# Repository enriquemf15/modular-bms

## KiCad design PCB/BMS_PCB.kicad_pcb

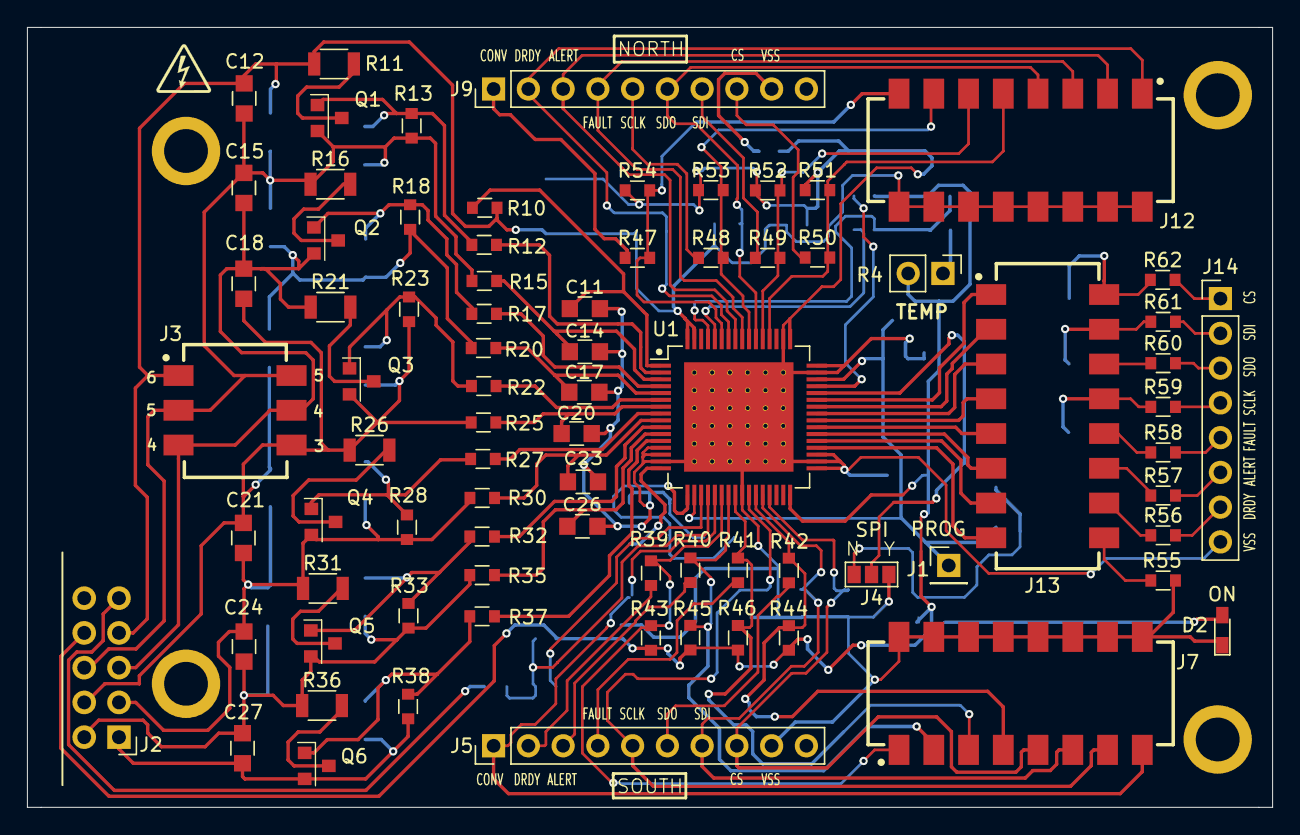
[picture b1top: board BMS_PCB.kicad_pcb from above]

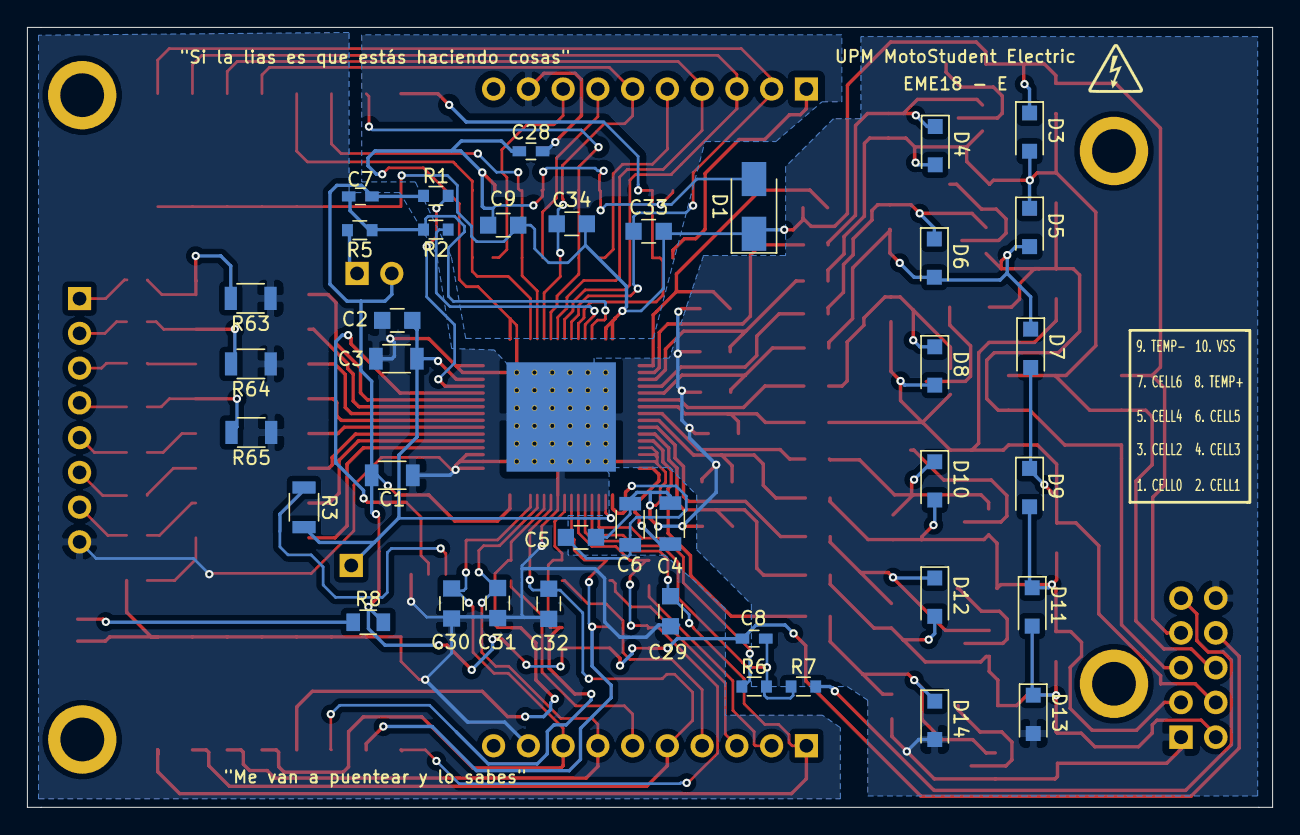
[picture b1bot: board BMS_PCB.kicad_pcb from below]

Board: 2 copper layers, 91.0 x 57.0 mm, 118 parts (39 on the bottom side), 93 nets.

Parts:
C1, C3, C6: 2,2 uF; C_1206
C2, C5, C9, C12, C15, C18, C21, C24, C27: 0,1 uF; C_0805_HandSoldering
C4: 10 uF; C_1206
C7, C8: 47 nF; C_0603_HandSoldering
C11, C14, C17, C20, C23, C26: 2.2 uF; C_0805_HandSoldering
C28: 10 nF; C_0603_HandSoldering
C29, C30, C31, C32, C33, C34: 33 pF; C_0805_HandSoldering
D1: TVS; D_SMA
D2: LED; LED_0603_HandSoldering
D3, D4, D5, D6, D7, D8, D9, D10, D11, D12, D13, D14: 5,1 V; D_SOD-123F
J1: Prog_Pin; Pin_Header_Straight_1x01_Pitch2.54mm
J2: Conn_01x10; IDC-Header_2x05_Pitch2.54mm_Angled
J3: Switch_3P_SPST; 1-1825059-2
J4: 3-pin solder bridge; GS3
J5, J9: Conn_01x10; Pin_Header_Straight_1x10_Pitch2.54mm
J7, J12, J13: Switch_8P_DIP_SPST; 4-1825059-1
J14: Conn_01x08; Pin_Header_Straight_1x08_Pitch2.54mm
Q1, Q2, Q3, Q4, Q5, Q6: IRLML6244; SOT95P237X112-3N
R1, R13, R18, R23, R28, R33, R38: 1M; R_0603_HandSoldering
R2, R6: 1,74K; R_0603_HandSoldering
R3, R63, R64, R65: 100K; R_1206
R4: NTC Thermistor; Pin_Header_Straight_1x02_Pitch2.54mm
R5, R7: 1,78K; R_0603_HandSoldering
R8: 1.5 K; R_0805_HandSoldering
R10, R12, R15, R17, R20, R22, R25, R27, R30, R32, R35, R37, R55: 1K; R_0603_HandSoldering
R11, R16, R21, R26, R31, R36: 33; R_1206
R39, R40, R41, R42, R47, R48, R49, R50, R56, R57, R58, R59, R60, R61, R62: 100; R_0603_HandSoldering
R43, R44, R45, R46: 560K; R_0603_HandSoldering
R51, R52, R53, R54: 3 M; R_0603_HandSoldering
U1: BQ76PL536A_Q1; HTQFP-64_1EP_10x10mm_Pitch0.5mm_ThermalPad

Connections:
/ALERT_H: J13.6, U1.38
/ALERT_N: J9.3, J12.2, U1.57
/ALERT_S: J7.2, R40.2, R45.2, U1.23
/BalanceCircuit/VC1_Input: C24.2, C27.1, D11.2, D12.2, D13.1, J2.2, Q5.2, R33.2, R35.2, R36.1
/BalanceCircuit/VC2_Input: C21.2, C24.1, D9.2, D10.2, D11.1, J2.3, Q4.2, R28.2, R30.2, R31.1
/CB1: R37.1, U1.12
/CB2: R32.1, U1.10
/CB3: R27.1, U1.8
/CB4: R22.1, U1.6
/CB5: R17.1, U1.4
/CB6: R12.1, U1.2
/CELL3: C18.2, C21.1, D7.2, D8.2, D9.1, J2.4, J3.6, Q3.2, R23.2, R25.2, R26.1
/CELL4: C15.2, C18.1, D5.2, D6.2, D7.1, J2.5, J3.3, J3.5, Q2.2, R18.2, R20.2, R21.1
/CELL5: C12.2, C15.1, D3.2, D4.2, D5.1, J2.6, J3.2, J3.4, Q1.2, R13.2, R15.2, R16.1
/CONV_H: J13.8, U1.36
/CONV_N: J12.8, R47.2, R54.2, U1.59
/CONV_S: C29.1, J5.1, J7.8, U1.21
/CS_H: J13.1, U1.43
/CS_N: J12.5, R50.2, R51.2, U1.52
/CS_S: C30.1, J5.8, J7.5, U1.29
/DRDY_H: J13.7, U1.37
/DRDY_N: C33.1, J9.2, J12.1, U1.58
/DRDY_S: J7.1, R39.2, R43.2, U1.22
/FAULT_H: J13.5, U1.39
/FAULT_N: J9.4, J12.3, U1.56
/FAULT_S: J7.3, R41.2, R46.2, U1.24
/HostCom/ALERT: J14.6, R57.2
/HostCom/CLK: J14.4, R59.2
/HostCom/CS: J14.1, R62.2
/HostCom/DRDY: J14.7, R56.2
/HostCom/FAULT: J14.5, R58.2
/HostCom/MISO: J14.3, R60.2
/HostCom/MOSI: J14.2, R61.2
/SCLK_H: J13.4, U1.40
/SCLK_N: J12.7, R48.2, R53.2, U1.55
/SCLK_S: C32.1, J5.5, J7.7, U1.26
/SDI_H: J13.2, U1.42
/SDI_N: J12.6, R49.2, R52.2, U1.53
/SDI_S: C31.1, J5.7, J7.6, U1.28
/SDO_H: J13.3, U1.41
/SDO_N: C34.1, J9.6, J12.4, U1.54
/SDO_S: J7.4, R42.2, R44.2, U1.27
/TEMP-: J2.9, R7.2
/VC1: C26.1, R35.1, U1.11
/VC2: C23.1, R30.1, U1.9
/VC3: C20.1, R25.1, U1.7
/VC4: C17.1, R20.1, U1.5
/VC5: C14.1, R15.1, U1.3
/VC6: C11.1, R10.1, U1.1
BAT: C9.1, C12.1, C33.2, C34.2, D1.1, D3.1, J2.7, J3.1, J12.9, J12.10, J12.11, J12.12, J12.13, J12.14, J12.15, J12.16, R10.2, R11.1, U1.63, U1.64
HOST: J4.2, U1.44
LDOD: C2.2, C3.2, J1.1, R3.2, U1.18, U1.46
unnamed: C4.1, U1.16
unnamed: C5.1, C6.1, U1.17
unnamed: C28.1, J9.9
unnamed: D2.2, R8.1
unnamed: D4.1, Q1.1, R12.2, R13.1
unnamed: D6.1, Q2.1, R17.2, R18.1
unnamed: D8.1, Q3.1, R22.2, R23.1
unnamed: D10.1, Q4.1, R27.2, R28.1
unnamed: D12.1, Q5.1, R32.2, R33.1
unnamed: D14.1, Q6.1, R37.2, R38.1
unnamed: J4.1, R3.1
unnamed: J5.2, R39.1
unnamed: J5.3, R40.1
unnamed: J5.4, R41.1
unnamed: J5.6, R42.1
unnamed: J9.1, R47.1
unnamed: J9.5, R48.1
unnamed: J9.7, R49.1
unnamed: J9.8, R50.1
unnamed: J13.9, R62.1, R63.2
unnamed: J13.10, R61.1, R64.2
unnamed: J13.11, R60.1
unnamed: J13.12, R59.1, R65.2
unnamed: J13.13, R58.1
unnamed: J13.14, R57.1
unnamed: J13.15, R56.1
unnamed: J13.16, R55.2
unnamed: Q1.3, R11.2
unnamed: Q2.3, R16.2
unnamed: Q3.3, R21.2
unnamed: Q4.3, R26.2
unnamed: Q5.3, R31.2
unnamed: Q6.3, R36.2
unnamed: R1.2, U1.45
unnamed: R4.1, R5.2
REG50: C1.2, C7.2, C8.2, J2.8, R1.1, R4.2, R8.2, R43.1, R44.1, R45.1, R46.1, U1.32
TS1+: C8.1, R6.2, R7.1, U1.20
TS1-: R6.1, U1.19
TS2+: C7.1, R2.2, R5.1, U1.61
TS2-: R2.1, U1.60
VSS: C1.1, C2.1, C3.1, C4.2, C5.2, C6.2, C9.2, C11.2, C14.2, C17.2, C20.2, C23.2, C26.2, C27.2, C28.2, C29.2, C30.2, C31.2, C32.2, D1.2, D2.1, D13.2, D14.2, J2.1, J2.10, J4.3, J5.9, J7.9, J7.10, J7.11, J7.12, J7.13, J7.14, J7.15, J7.16, J14.8, Q6.2, R38.2, R51.1, R52.1, R53.1, R54.1, R55.1, R63.1, R64.1, R65.1, U1.13, U1.14, U1.15, U1.25, U1.33, U1.34, U1.35, U1.47, U1.48, U1.49, U1.50, U1.65

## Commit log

2018-08-12 PCB
    Archivos completos de la PCB en el programa KiCad.
2018-08-12 Gerber, Librerias, 3D, BOM
    Archivos añadidos para Kicad, los archivos Gerber generados, la lista de materiales completa utilizada y un modelo 3D de un posible montaje de las PCB
